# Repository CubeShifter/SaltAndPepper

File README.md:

# SaltAndPepper
A 65% split keyboard because i was bored.

Features:
65% keyboard but split
EC11 rotary encoder on right side
You can theoretically do wireless, i made lil cutouts and power switches it should last long  
oh its hotswap i guess

i tried to make a fairly low power keyboard so you dont have to keep it charging. it uses nice nanos which are low power microcontrollers, uh they work really well for this design and yeah.

screenshots of pcb

i didnt really want to learn how to use heirarchal sheets or wtv so i mean its finne. 

assembly:

look at bom
buy stuff in bom
also order pcbs
solder solder solder
yay
(its pretty easy to follow i belive in you)

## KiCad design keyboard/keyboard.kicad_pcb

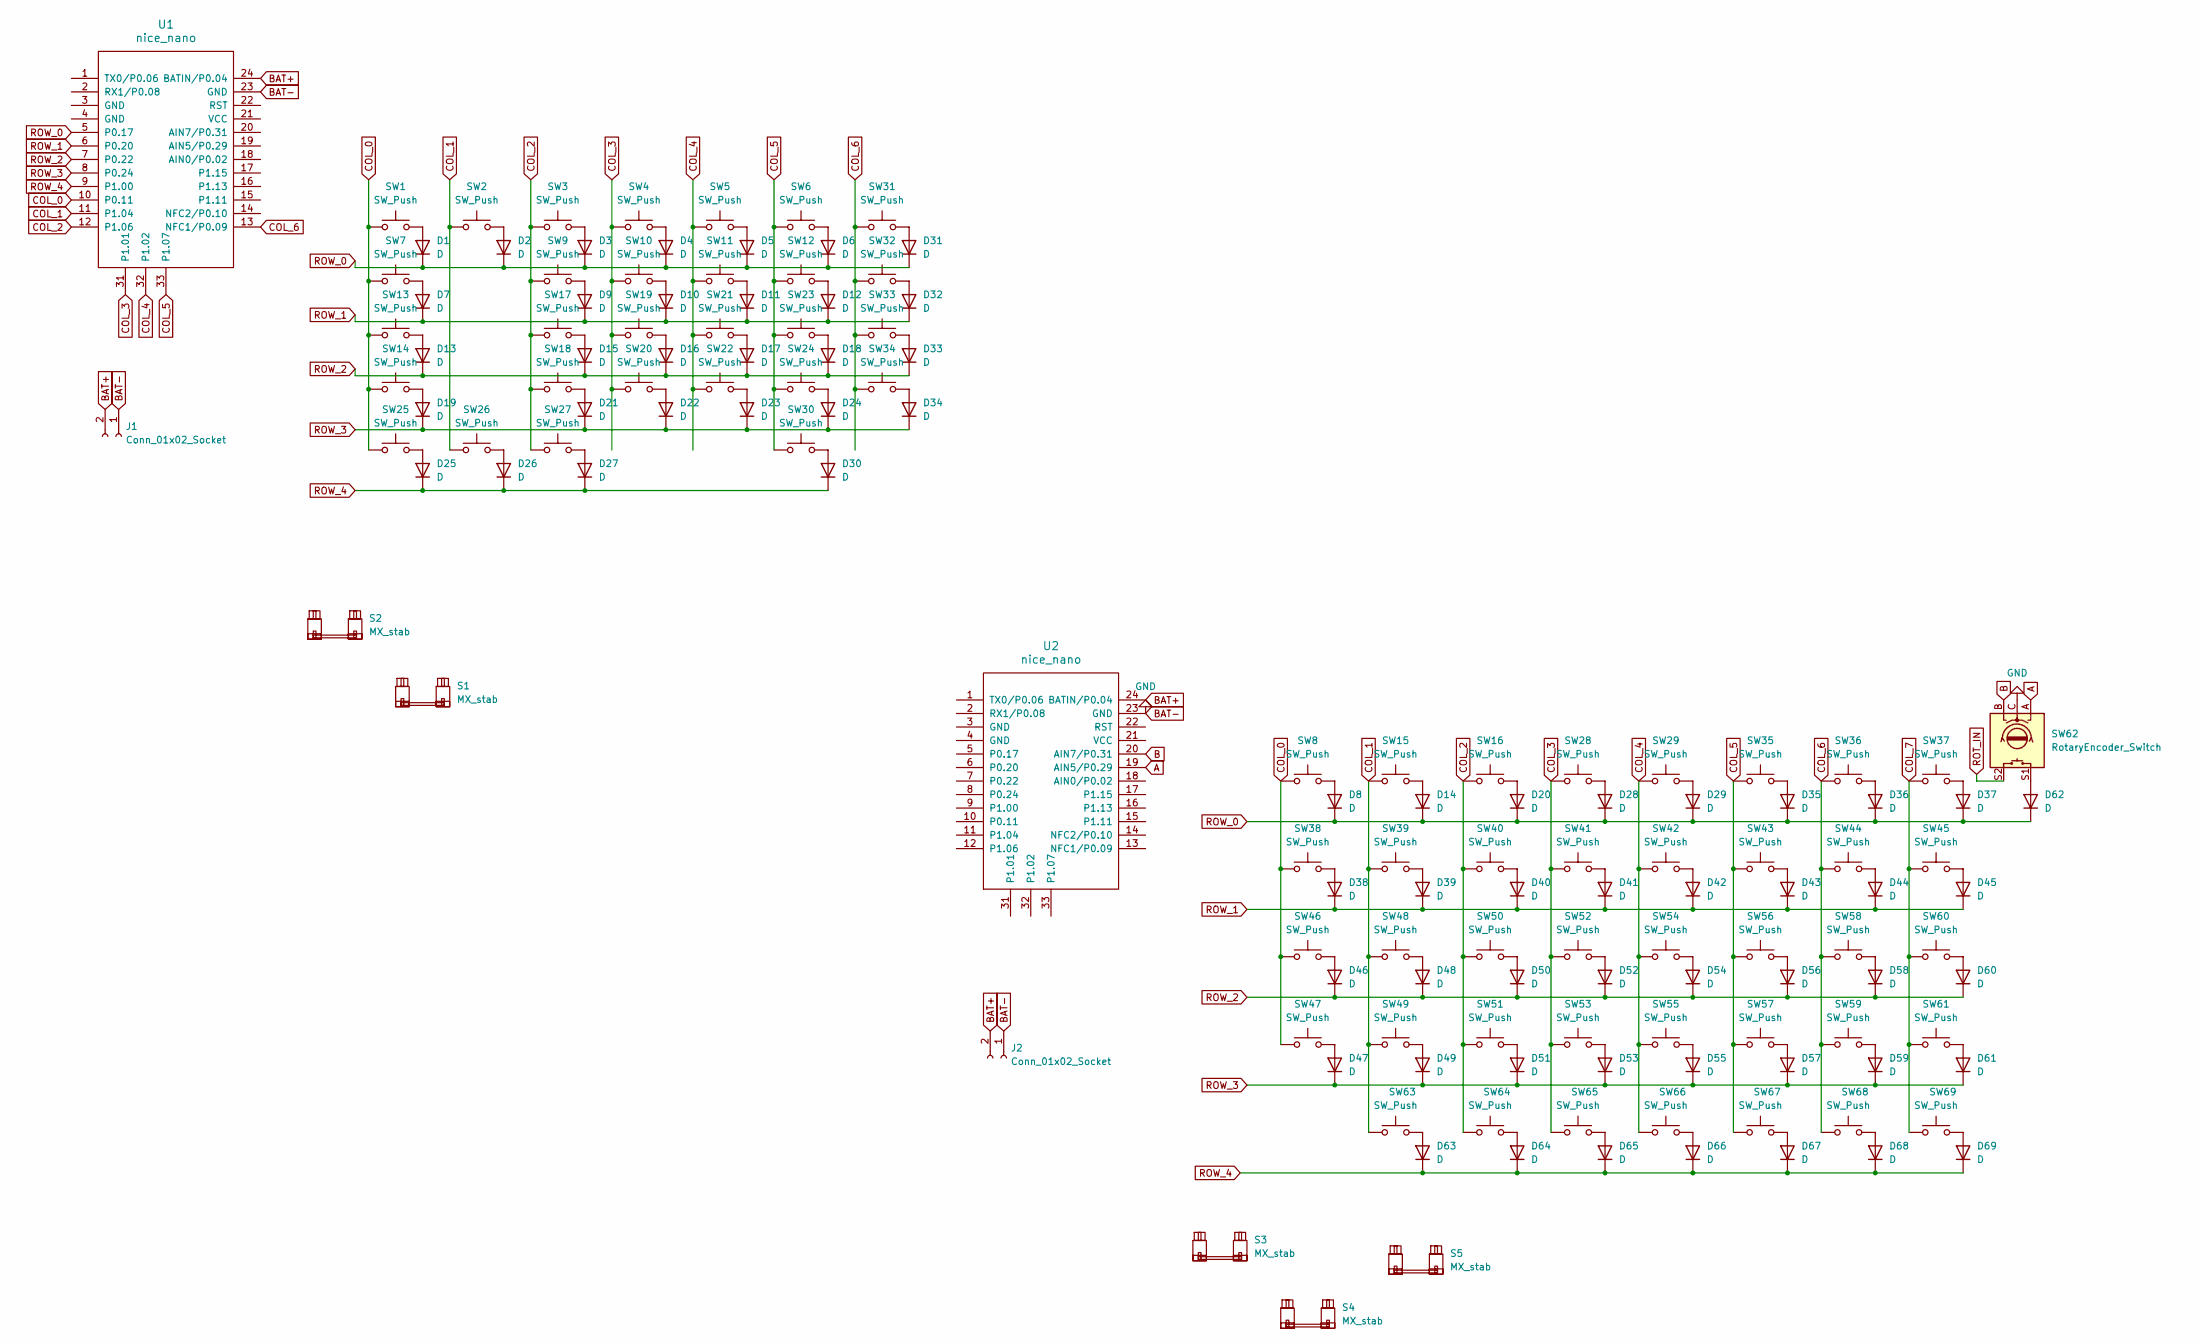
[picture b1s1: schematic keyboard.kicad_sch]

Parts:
D1, D2, D3, D4, D5, D6, D7, D8, D9, D10, D11, D12, D13, D14, D15, D16, D17, D18, D19, D20, D21, D22, D23, D24, D25, D26, D27, D28, D29, D30, D31, D32, D33, D34, D35, D36, D37, D38, D39, D40, D41, D42, D43, D44, D45, D46, D47, D48, D49, D50, D51, D52, D53, D54, D55, D56, D57, D58, D59, D60, D61, D62, D63, D64, D65, D66, D67, D68, D69: D; D_DO-35_SOD27_P7.62mm_Horizontal
J1, J2: Conn_01x02_Socket; PinSocket_1x02_P2.54mm_Horizontal
S1, S2, S3, S4: MX_stab; STAB_MX_2u
S5: MX_stab; STAB_MX_P_2.25u
SW1, SW2, SW3, SW4, SW5, SW6, SW7, SW8, SW9, SW10, SW11, SW12, SW13, SW14, SW15, SW16, SW17, SW18, SW19, SW20, SW21, SW22, SW23, SW24, SW25, SW26, SW27, SW28, SW29, SW30, SW31, SW32, SW33, SW34, SW35, SW36, SW37, SW38, SW39, SW40, SW41, SW42, SW43, SW44, SW45, SW46, SW47, SW48, SW49, SW50, SW51, SW52, SW53, SW54, SW55, SW56, SW57, SW58, SW59, SW60, SW61, SW63, SW64, SW65, SW66, SW67, SW68, SW69: SW_Push; SW_MX_HS_CPG151101S11_1u
SW62: RotaryEncoder_Switch; RotaryEncoder_Alps_EC11E-Switch_Vertical_H20mm
U1, U2: nice_nano

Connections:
A: SW62.A, U2.19 (AIN5/P0.29)
B: SW62.B, U2.20 (AIN7/P0.31)
BAT+: J1.2, J2.2, U1.24 (BATIN/P0.04), U2.24 (BATIN/P0.04)
BAT-: J1.1, J2.1, SW62.C, U1.23 (GND), U2.23 (GND)
COL_0: SW1.1, SW7.1, SW8.1, SW13.1, SW14.1, SW25.1, SW38.1, SW46.1, SW47.1, U1.10 (P0.11), U2.10 (P0.11)
COL_1: SW2.1, SW15.1, SW26.1, SW39.1, SW48.1, SW49.1, SW63.1, U1.11 (P1.04), U2.11 (P1.04)
COL_2: SW3.1, SW9.1, SW16.1, SW17.1, SW18.1, SW27.1, SW40.1, SW50.1, SW51.1, SW64.1, U1.12 (P1.06), U2.12 (P1.06)
COL_3: SW4.1, SW10.1, SW19.1, SW20.1, SW28.1, SW41.1, SW52.1, SW53.1, SW65.1, U1.31 (P1.01), U2.31 (P1.01)
COL_4: SW5.1, SW11.1, SW21.1, SW22.1, SW29.1, SW42.1, SW54.1, SW55.1, SW66.1, U1.32 (P1.02), U2.32 (P1.02)
COL_5: SW6.1, SW12.1, SW23.1, SW24.1, SW30.1, SW35.1, SW43.1, SW56.1, SW57.1, SW67.1, U1.33 (P1.07), U2.33 (P1.07)
COL_6: SW31.1, SW32.1, SW33.1, SW34.1, SW36.1, SW44.1, SW58.1, SW59.1, SW68.1, U1.13 (NFC1/P0.09), U2.13 (NFC1/P0.09)
COL_7: SW37.1, SW45.1, SW60.1, SW61.1, SW69.1, U2.14 (NFC2/P0.10)
unnamed: D1.2 (A), SW1.2
unnamed: D2.2 (A), SW2.2
unnamed: D3.2 (A), SW3.2
unnamed: D4.2 (A), SW4.2
unnamed: D5.2 (A), SW5.2
unnamed: D6.2 (A), SW6.2
unnamed: D7.2 (A), SW7.2
unnamed: D8.2 (A), SW8.2
unnamed: D9.2 (A), SW9.2
unnamed: D10.2 (A), SW10.2
unnamed: D11.2 (A), SW11.2
unnamed: D12.2 (A), SW12.2
unnamed: D13.2 (A), SW13.2
unnamed: D14.2 (A), SW15.2
unnamed: D15.2 (A), SW17.2
unnamed: D16.2 (A), SW19.2
unnamed: D17.2 (A), SW21.2
unnamed: D18.2 (A), SW23.2
unnamed: D19.2 (A), SW14.2
unnamed: D20.2 (A), SW16.2
unnamed: D21.2 (A), SW18.2
unnamed: D22.2 (A), SW20.2
unnamed: D23.2 (A), SW22.2
unnamed: D24.2 (A), SW24.2
unnamed: D25.2 (A), SW25.2
unnamed: D26.2 (A), SW26.2
unnamed: D27.2 (A), SW27.2
unnamed: D28.2 (A), SW28.2
unnamed: D29.2 (A), SW29.2
unnamed: D30.2 (A), SW30.2
unnamed: D31.2 (A), SW31.2
unnamed: D32.2 (A), SW32.2
unnamed: D33.2 (A), SW33.2
unnamed: D34.2 (A), SW34.2
unnamed: D35.2 (A), SW35.2
unnamed: D36.2 (A), SW36.2
unnamed: D37.2 (A), SW37.2
unnamed: D38.2 (A), SW38.2
unnamed: D39.2 (A), SW39.2
unnamed: D40.2 (A), SW40.2
unnamed: D41.2 (A), SW41.2
unnamed: D42.2 (A), SW42.2
unnamed: D43.2 (A), SW43.2
unnamed: D44.2 (A), SW44.2
unnamed: D45.2 (A), SW45.2
unnamed: D46.2 (A), SW46.2
unnamed: D47.2 (A), SW47.2
unnamed: D48.2 (A), SW48.2
unnamed: D49.2 (A), SW49.2
unnamed: D50.2 (A), SW50.2
unnamed: D51.2 (A), SW51.2
unnamed: D52.2 (A), SW52.2
unnamed: D53.2 (A), SW53.2
unnamed: D54.2 (A), SW54.2
unnamed: D55.2 (A), SW55.2
unnamed: D56.2 (A), SW56.2
unnamed: D57.2 (A), SW57.2
unnamed: D58.2 (A), SW58.2
unnamed: D59.2 (A), SW59.2
unnamed: D60.2 (A), SW60.2
unnamed: D61.2 (A), SW61.2
unnamed: D62.2 (A), SW62.S1
unnamed: D63.2 (A), SW63.2
unnamed: D64.2 (A), SW64.2
unnamed: D65.2 (A), SW65.2
unnamed: D66.2 (A), SW66.2
unnamed: D67.2 (A), SW67.2
unnamed: D68.2 (A), SW68.2
unnamed: D69.2 (A), SW69.2
ROT_IN: SW62.S2
ROW_0: D1.1 (K), D2.1 (K), D3.1 (K), D4.1 (K), D5.1 (K), D6.1 (K), D8.1 (K), D14.1 (K), D20.1 (K), D28.1 (K), D29.1 (K), D31.1 (K), D35.1 (K), D36.1 (K), D37.1 (K), D62.1 (K), U1.5 (P0.17), U2.5 (P0.17)
ROW_1: D7.1 (K), D9.1 (K), D10.1 (K), D11.1 (K), D12.1 (K), D32.1 (K), D38.1 (K), D39.1 (K), D40.1 (K), D41.1 (K), D42.1 (K), D43.1 (K), D44.1 (K), D45.1 (K), U1.6 (P0.20), U2.6 (P0.20)
ROW_2: D13.1 (K), D15.1 (K), D16.1 (K), D17.1 (K), D18.1 (K), D33.1 (K), D46.1 (K), D48.1 (K), D50.1 (K), D52.1 (K), D54.1 (K), D56.1 (K), D58.1 (K), D60.1 (K), U1.7 (P0.22), U2.7 (P0.22)
ROW_3: D19.1 (K), D21.1 (K), D22.1 (K), D23.1 (K), D24.1 (K), D34.1 (K), D47.1 (K), D49.1 (K), D51.1 (K), D53.1 (K), D55.1 (K), D57.1 (K), D59.1 (K), D61.1 (K), U1.8 (P0.24), U2.8 (P0.24)
ROW_4: D25.1 (K), D26.1 (K), D27.1 (K), D30.1 (K), D63.1 (K), D64.1 (K), D65.1 (K), D66.1 (K), D67.1 (K), D68.1 (K), D69.1 (K), U1.9 (P1.00), U2.9 (P1.00)

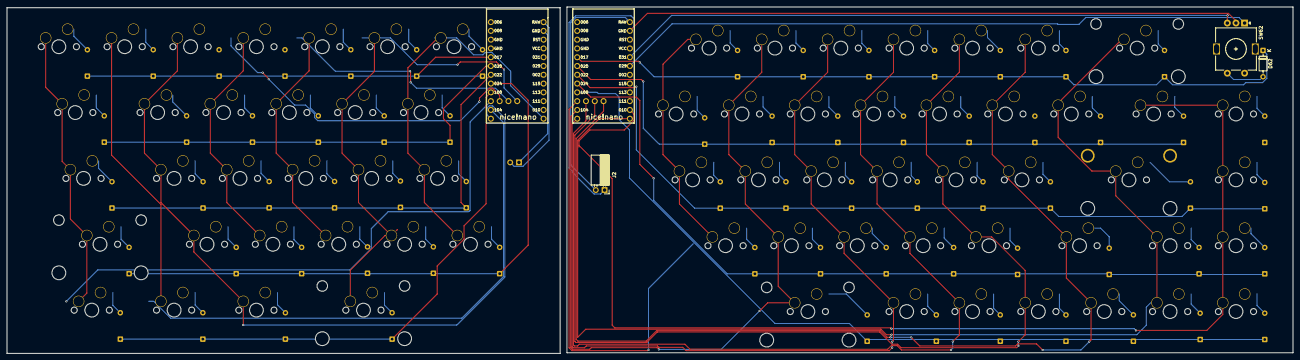
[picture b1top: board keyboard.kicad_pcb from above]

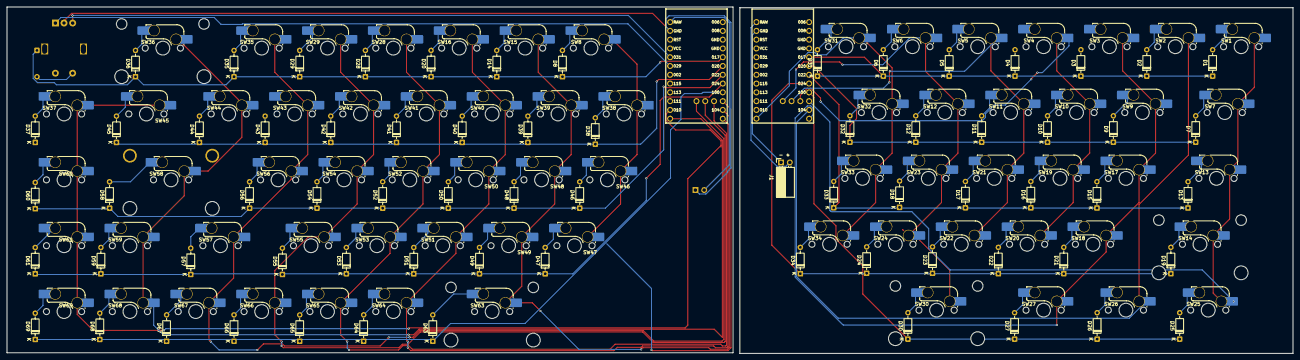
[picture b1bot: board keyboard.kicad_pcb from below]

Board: 2 copper layers, 372.0 x 100.2 mm, 148 parts (137 on the bottom side), 86 nets.

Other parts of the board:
S2#2: MX_stab; STAB_MX_2u
